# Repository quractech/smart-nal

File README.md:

# smart Nal
Smart Nal enables ON and OFF functionality for LED ceiling lamp using Bluetooth or normal light switch. <br>

watch the following YouTube channel for more information. </br>
https://www.youtube.com/embed/videoseries?list=PLivrBlTrqPpaUyPcGpUUAaZgcAJCYTLqt
 </br>

schematic of the Smart Nal Hardware. <br>
https://github.com/quractech/smart-nal/blob/2a30d1d0165a11da4ee4c517b96f4f8cc76464df/smartNal.pdf

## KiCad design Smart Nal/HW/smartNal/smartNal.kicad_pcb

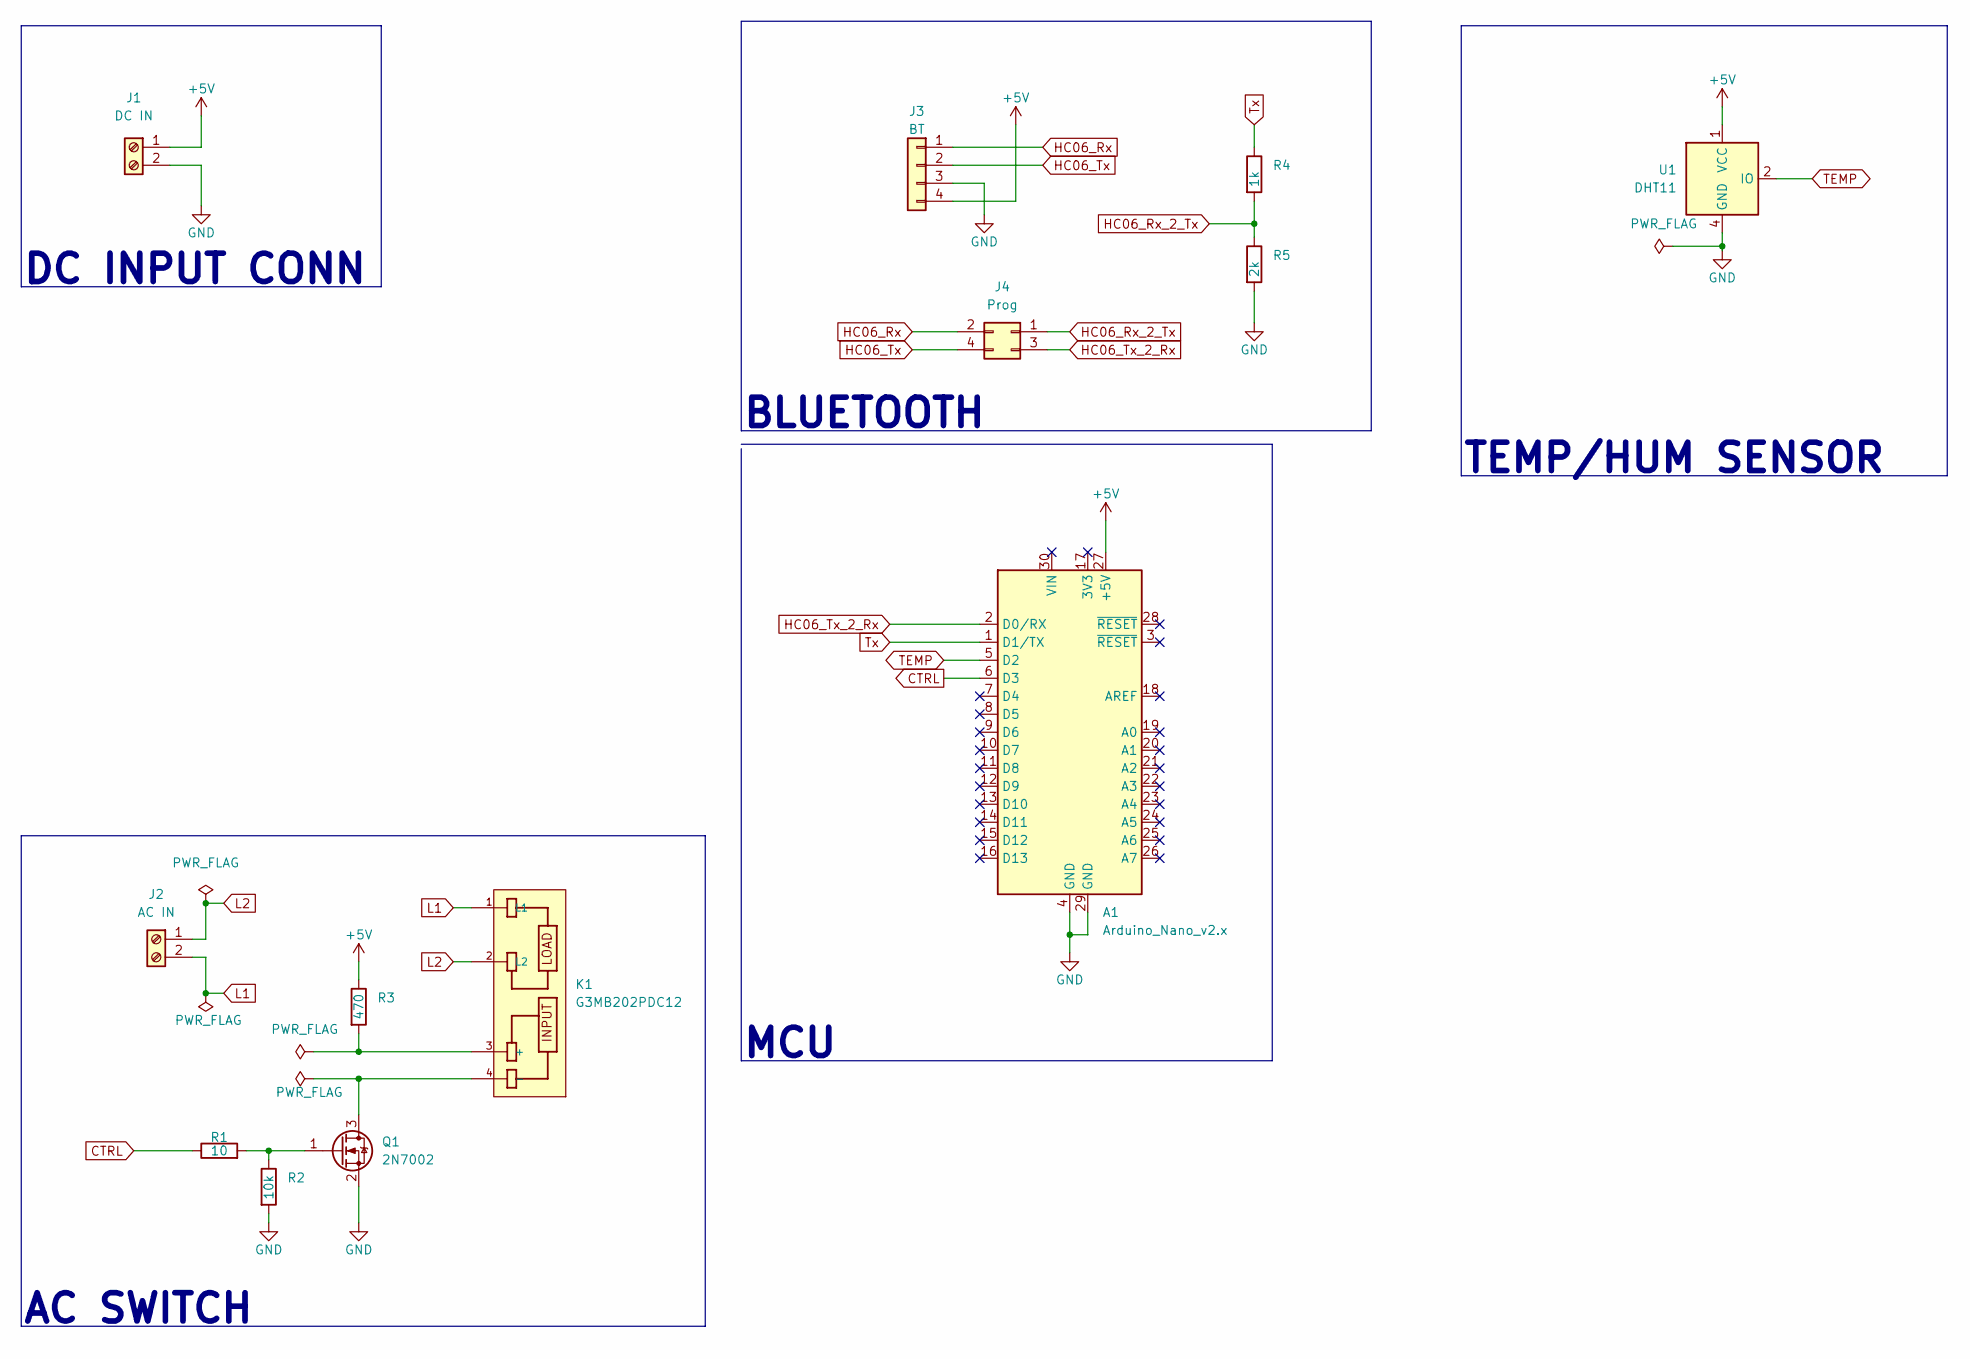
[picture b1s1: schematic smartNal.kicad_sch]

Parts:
A1: Arduino_Nano_v2.x; Arduino_Nano
J1: DC IN; TerminalBlock_bornier-2_P5.08mm
J2: AC IN; TerminalBlock_bornier-2_P5.08mm
J3: BT; PinHeader_1x04_P2.54mm_Vertical
J4: Prog; PinHeader_2x02_P2.54mm_Vertical
K1: G3MB202PDC12; RELAY_G3MB202PDC12; PARTREV N/A
Q1: 2N7002; SOT-23; MFR.Part # 2N7002; JLCPCB Part # C8545
R1: 10; R_0603_1608Metric
R2: 10k; R_0603_1608Metric
R3: 470; R_0603_1608Metric
R4: 1k; R_0603_1608Metric
R5: 2k; R_0603_1608Metric
U1: DHT11; Aosong_DHT11_5.5x12.0_P2.54mm

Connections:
+5V: A1.27 (+5V), J1.1, J3.4, R3.1, U1.1 (VCC)
CTRL: A1.6 (D3), R1.1
GND: A1.4 (GND), A1.29 (GND), J1.2, J3.3, Q1.2 (S), R2.2, R5.2, U1.4 (GND)
HC06_Rx: J3.1, J4.2
HC06_Rx_2_Tx: J4.1, R4.2, R5.1
HC06_Tx: J3.2, J4.4
HC06_Tx_2_Rx: A1.2 (D0/RX), J4.3
L1: J2.2, K1.1 (L1)
L2: J2.1, K1.2 (L2)
unnamed: K1.3 (+), R3.2
unnamed: K1.4 (-), Q1.3 (D)
unnamed: Q1.1 (G), R1.2, R2.1
TEMP: A1.5 (D2), U1.2 (IO)
Tx: A1.1 (D1/TX), R4.1

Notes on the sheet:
BLUETOOTH
DC INPUT CONN
TEMP/HUM SENSOR
AC SWITCH
MCU

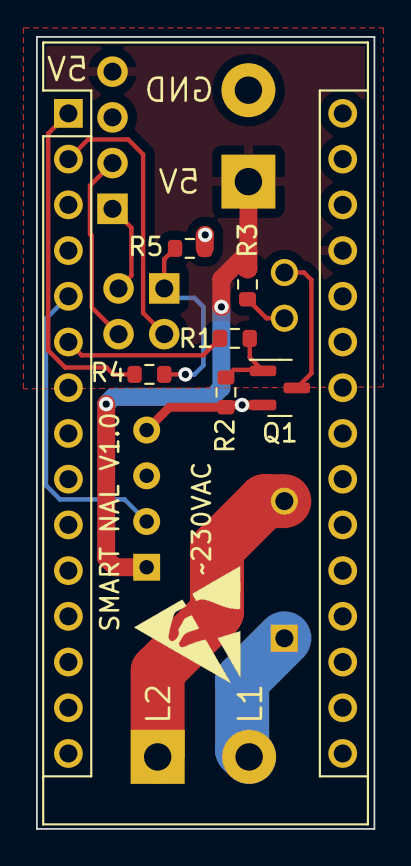
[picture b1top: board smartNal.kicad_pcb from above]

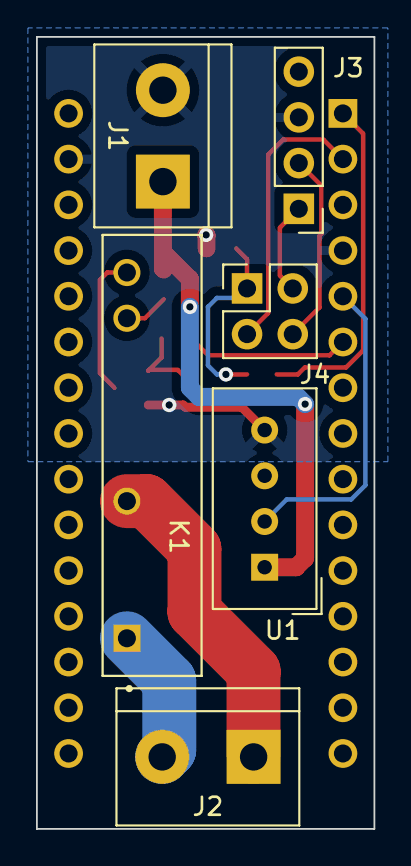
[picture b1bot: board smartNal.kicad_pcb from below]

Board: 2 copper layers, 18.8 x 44.0 mm, 13 parts (6 on the bottom side), 14 nets.

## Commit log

2022-07-23 Create CNAME
